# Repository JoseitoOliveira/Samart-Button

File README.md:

# Samart Button 🕹
 Dispositivo de comunicação que ajuda idosos a solicitarem atendimento dos seus cuidadores e/ou responsáveis de maneira rápida, prática e eficiente.

O dispositivo acima se comunica por meio de TCP/IP com um computador que exibe as solicitações.

Foi desenvolvido um software em C# que exibe as notificações recebidas. Infelizmente eu perdi esse código ao formatar o computador e não fazer backup. 🙄

Cada botão do dispositivo representa uma mensagem que pode ser customizada, junto da cor e o número de identificação. Estas e outras configurações são realizadas por meio de uma página web criada pelo dispositivo.

Um layout mais compacto da placa foi desenvolvido posteriormente, mas não chegou a ser produzido.

As configurações são salvas em memória não volátil, que no caso do ESP8266 é flash. Essas configurações ficam armazenadas em memória da seguinte forma:

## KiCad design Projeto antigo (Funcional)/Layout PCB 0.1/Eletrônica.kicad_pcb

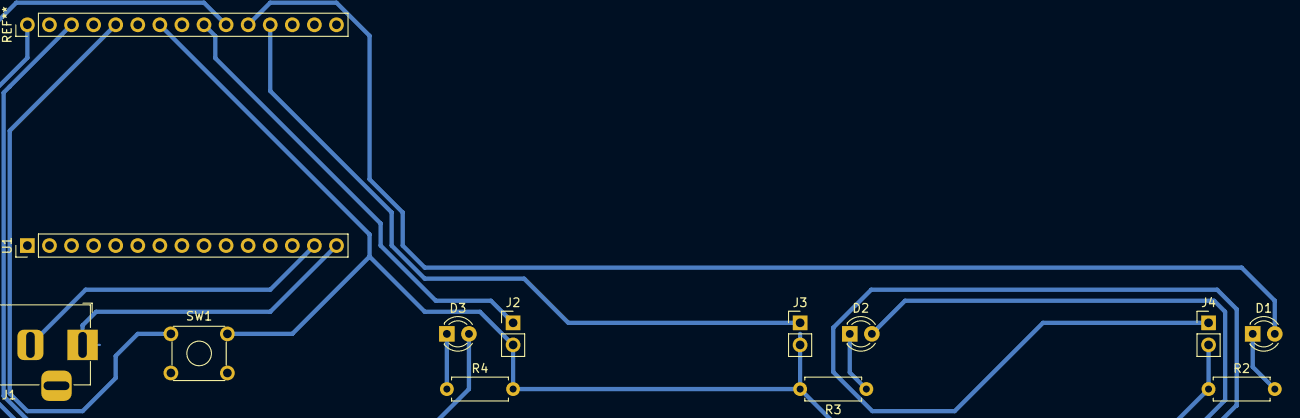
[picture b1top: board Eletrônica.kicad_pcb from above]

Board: 2 copper layers, 12 parts (0 on the bottom side), 13 nets.

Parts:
D1, D2, D3: LED; LED_D3.0mm
J1: Jack-DC; BarrelJack_Horizontal
J2, J3, J4: Conn_01x02_Female; PinHeader_1x02_P2.54mm_Vertical
R2, R3, R4: R; R_Axial_DIN0207_L6.3mm_D2.5mm_P7.62mm_Horizontal
SW1: SW_Push_Dual; SW_TH_Tactile_Omron_B3F-10xx
U1: NodeMCU_v1.0; nodeMCU

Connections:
unnamed: D1.1, R2.2
unnamed: D1.2, U1.25
unnamed: D2.1, R3.1
unnamed: D2.2, U1.15
unnamed: D3.1, R4.1
unnamed: D3.2, U1.17
unnamed: J1.1, U1.14
unnamed: J1.2, U1.13
unnamed: J2.1, U1.23
unnamed: J2.2, J3.2, J4.2, R2.1, R3.2, R4.2, SW1.2, U1.21
unnamed: J3.1, U1.26
unnamed: J4.1, U1.24
unnamed: SW1.1, U1.19

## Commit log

2021-02-20 Commit inicial
